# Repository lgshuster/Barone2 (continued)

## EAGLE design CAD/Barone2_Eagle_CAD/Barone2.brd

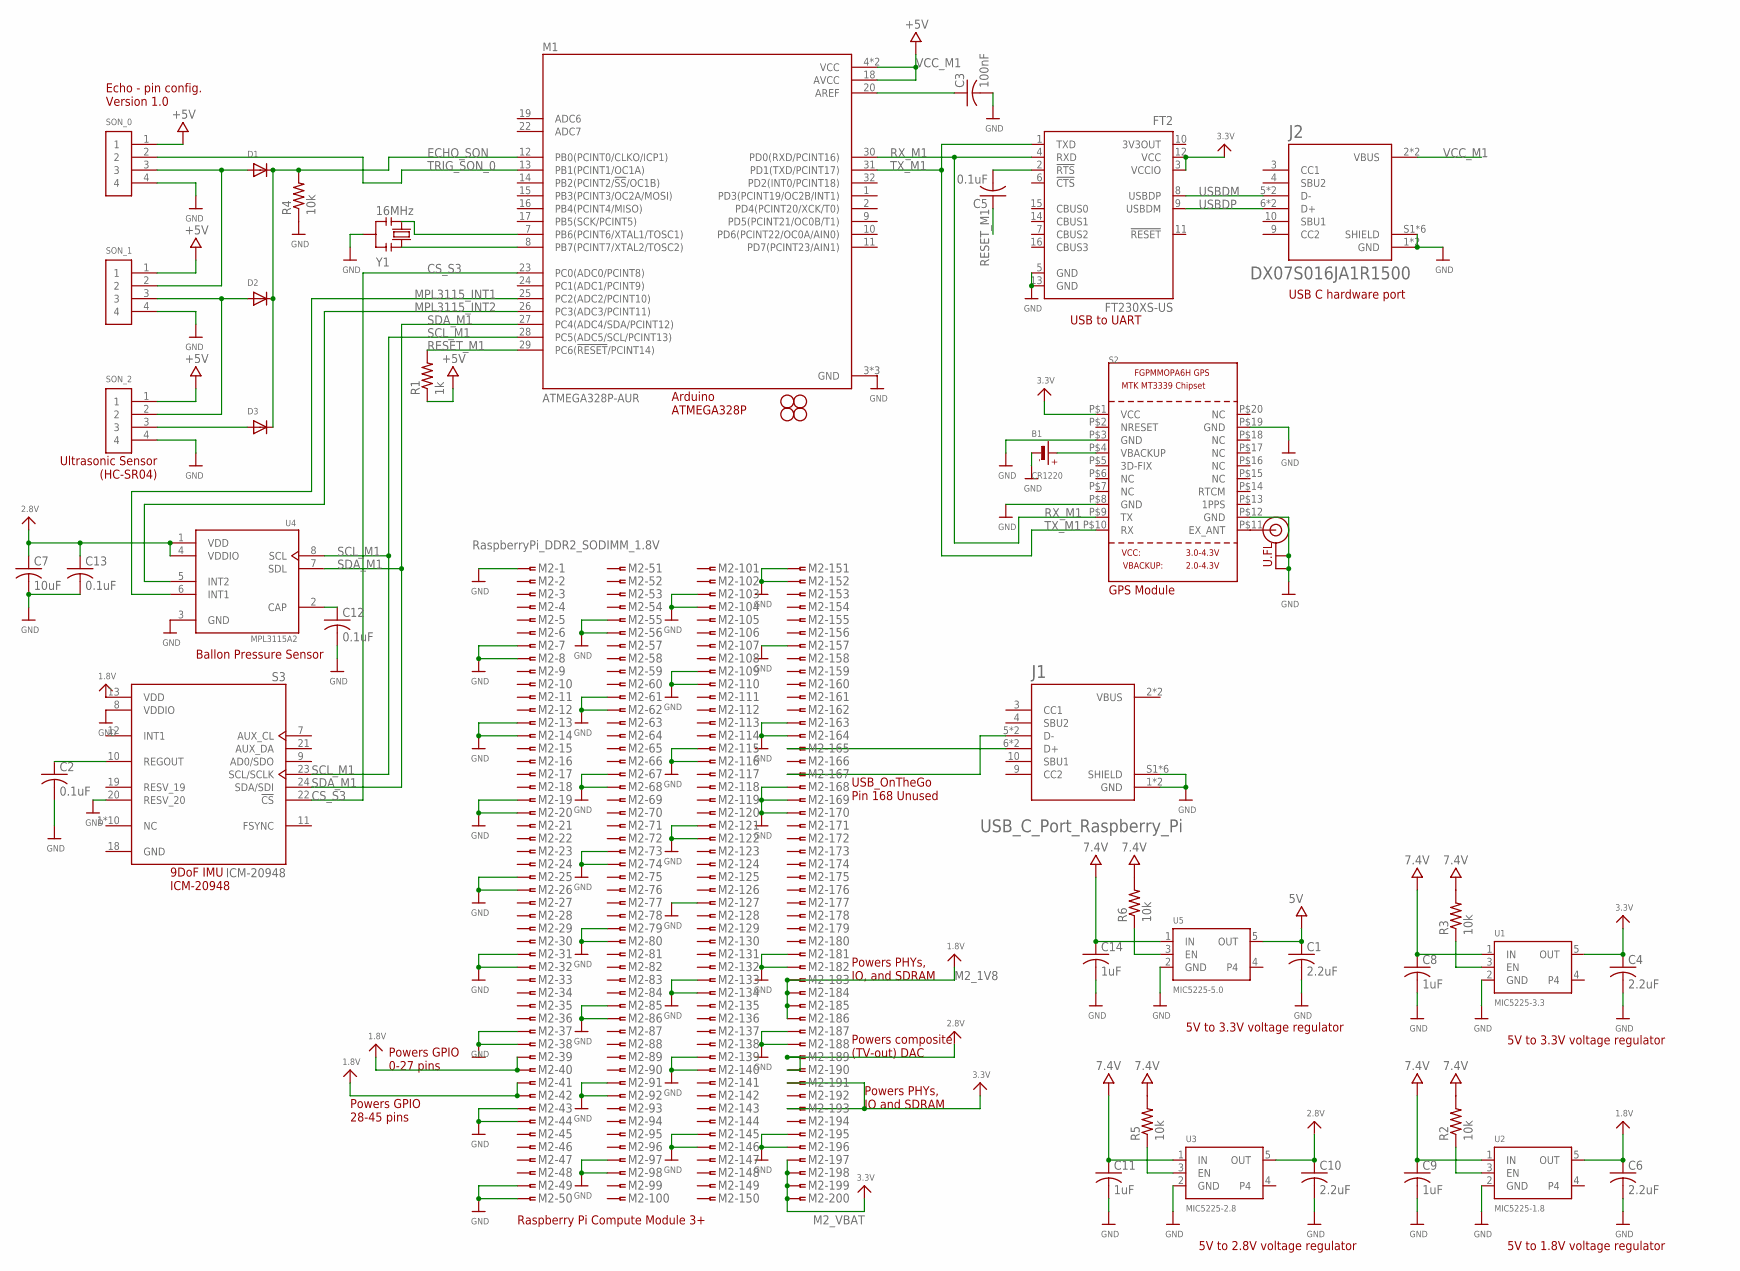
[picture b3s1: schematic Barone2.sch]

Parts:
B1: CR1220
C1, C4, C6, C10: 2.2uF; C0805
C2, C5, C12, C13: 0.1uF; C0805
C3: 100nF; C0805
C7: 10uF; C0805
C8, C9, C11, C14: 1uF; C0805
D1, D2, D3: DIODESOD-323F; SOD-323F
FT2: FT230XS-US; SSOP16
H1, H2, H3, H4: STAND-OFF
J1: USB_C_Port_Raspberry_Pi; JAE_DX07S016JA1R1500
J2: DX07S016JA1R1500; JAE_DX07S016JA1R1500
M1: ATMEGA328P-AUR; QFP80P900X900X120-32N
M2: RaspberryPi_DDR2_SODIMM_1.8V; SLOT-1376408-1_1.8V
R1: 1k; R0805W
R2, R3, R4, R5, R6: 10k; R0805W
S2: GPS_FGPMMOPA6H; FGPMMOPA6H
S3: ICM-20948; QFN40P300X300X105-24N
SON_0, SON_1, SON_2: 1X4-BIG; 1X04-BIG
U1: MIC5225-3.3; SOT23-5
U2: MIC5225-1.8; SOT23-5
U3: MIC5225-2.8; SOT23-5
U4: MPL3115A2; PSON125P300X500X120-8N
U5: MIC5225-5.0; SOT23-5
U.FL: U.FL
Y1: 16MHz; RESONATOR

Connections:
+5V: C14.1, R1.1, R2.2, R3.2, R5.2, R6.2, SON_0.1, SON_1.1, SON_2.1, U5.1 (IN)
CS_S3: M1.23 (PC0(ADC0/PCINT8)), S3.22 (!CS)
ECHO_SON: D1.C, D2.C, D3.C, M1.12 (PB0(PCINT0/CLKO/ICP1)), R4.2
GND: B1.-, C1.2, C2.2, C3.2, C4.2, C6.2, C7.2, C8.2, C9.2, C10.2, C11.2, C12.2, C13.2, C14.2, FT2.5 (GND), FT2.13 (GND), J1.1 (GND), J1.12 (GND), J1.S1 (SHIELD), J1.S2 (SHIELD), J1.S3 (SHIELD), J1.S4 (SHIELD), J1.S5 (SHIELD), J1.S6 (SHIELD), J2.1 (GND), J2.12 (GND), J2.S1 (SHIELD), J2.S2 (SHIELD), J2.S3 (SHIELD), J2.S4 (SHIELD), J2.S5 (SHIELD), J2.S6 (SHIELD), M1.3 (GND), M1.5 (GND), M1.21 (GND), M2.1, M2.7, M2.8, M2.13, M2.14, M2.19, M2.20, M2.25, M2.26, M2.31, M2.32, M2.37, M2.38, M2.43, M2.44, M2.49, M2.50, M2.55, M2.56, M2.61, M2.62, M2.67, M2.68, M2.73, M2.74, M2.79, M2.80, M2.85, M2.86, M2.91, M2.92, M2.97, M2.98, M2.103, M2.104, M2.109, M2.110, M2.115, M2.116, M2.121, M2.122, M2.127, M2.133, M2.134, M2.139, M2.140, M2.145, M2.146, M2.151, M2.152, M2.157, M2.163, M2.164, M2.168, M2.169, M2.170, M2.181, M2.182, M2.187, M2.188, M2.195, M2.196, R4.1, S2.P$3 (GND), S2.P$8 (GND), S2.P$19 (GND), S3.8 (VDDIO), S3.18 (GND), S3.20 (RESV_20), SON_0.4, SON_1.4, SON_2.4, U1.2 (GND), U2.2 (GND), U3.2 (GND), U4.3 (GND), U5.2 (GND), Y1.2
M2_1V8: M2.183, M2.184, M2.185, M2.186
M2_VBAT: M2.197, M2.198, M2.199, M2.200
MPL3115_INT1: M1.25 (PC2(ADC2/PCINT10)), U4.6 (INT1)
MPL3115_INT2: M1.26 (PC3(ADC3/PCINT11)), U4.5 (INT2)
unnamed: C3.1, M1.20 (AREF)
unnamed: S2.P$12 (GND), U.FL.P$1 (GND), U.FL.P$2 (GND)
unnamed: S2.P$11 (EX_ANT), U.FL.P$3 (SIGNAL)
unnamed: R3.1, U1.3 (EN)
unnamed: B1.+$1 (+), B1.+$2 (+), S2.P$4 (VBACKUP)
unnamed: R2.1, U2.3 (EN)
unnamed: J1.6 (D+), J1.7 (D+), M2.165
unnamed: J1.5 (D-), J1.8 (D-), M2.167
unnamed: M2.39, M2.40
unnamed: C12.1, U4.2 (CAP)
unnamed: R6.1, U5.3 (EN)
unnamed: R5.1, U3.3 (EN)
unnamed: D1.A, SON_0.3, SON_1.2
unnamed: D2.A, SON_1.3, SON_2.2
unnamed: M2.41, M2.42
unnamed: C8.1, U1.1 (IN)
unnamed: C5.2, FT2.2 (!RTS)
unnamed: D3.A, SON_2.3
unnamed: C9.1, U2.1 (IN)
unnamed: C11.1, U3.1 (IN)
unnamed: M1.7 (PB6(PCINT6/XTAL1/TOSC1)), Y1.3
unnamed: M1.8 (PB7(PCINT7/XTAL2/TOSC2)), Y1.1
unnamed: C2.1, S3.10 (REGOUT)
OUT: C1.1, C4.1, C6.1, C10.1, U1.5 (OUT), U2.5 (OUT), U3.5 (OUT), U5.5 (OUT)
RESET_M1: C5.1, M1.29 (PC6(!RESET!/PCINT14)), R1.2
RX_M1: FT2.4 (RXD), M1.30 (PD0(RXD/PCINT16)), S2.P$9 (TX)
SCL_M1: M1.28 (PC5(ADC5/SCL/PCINT13)), S3.23 (SCL/SCLK), U4.8 (SCL)
SDA_M1: M1.27 (PC4(ADC4/SDA/PCINT12)), S3.24 (SDA/SDI), U4.7 (SDL)
TRIG_SON_0: M1.13 (PB1(PCINT1/OC1A)), SON_0.2
TX_M1: FT2.1 (TXD), M1.31 (PD1(TXD/PCINT17)), S2.P$10 (RX)
USBDM: FT2.8 (USBDP), J2.5 (D-), J2.8 (D-)
USBDP: FT2.9 (USBDM), J2.6 (D+), J2.7 (D+)
VBUS: J1.2 (VBUS), J1.11 (VBUS)
VCC_M1: J2.2 (VBUS), J2.11 (VBUS), M1.4 (VCC), M1.6 (VCC), M1.18 (AVCC)
VIN: C7.1, C13.1, FT2.3 (VCCIO), FT2.12 (VCC), M2.189, M2.190, M2.191, M2.193, S2.P$1 (VCC), S3.13 (VDD), U4.1 (VDD), U4.4 (VDDIO)

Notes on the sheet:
9DoF IMU ICM-20948
Ultrasonic Sensor (HC-SR04)
USB to UART
Arduino ATMEGA328P
GPS Module
USB C hardware port
5V to 3.3V voltage regulator
Ballon Pressure Sensor
Raspberry Pi Compute Module 3+
5V to 1.8V voltage regulator
USB_OnTheGo Pin 168 Unused
Powers PHYs, IO and SDRAM
U.FL
Powers PHYs, IO, and SDRAM
5V to 2.8V voltage regulator
Powers composite (TV-out) DAC
Powers GPIO 0-27 pins
Powers GPIO 28-45 pins
Echo - pin config. Version 1.0

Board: 4 copper layers, 45 parts (0 on the bottom side), 43 nets, no tracks yet.

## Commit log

2021-03-06 Set up folders for ECE121 work
2021-03-06 Added folder for ECE121 Lab Manuals
2021-03-06 Create Lab2
2021-03-07 Create Family Reference Manual
2021-03-13 Deleted all previous files in Ryan's folder, added entire git repository from ECE121
2021-03-13 Wiring diagram and Board diagram V1.9
2021-03-15 wiring up board
2021-03-19 Added ballon pressure sensor, oscillators, logic level convers
2021-03-21 added logic level converter for interupt pin of IMU
2021-03-28 Added Transmitter pinout
2021-03-30 Fixing ECE121 source code
2021-03-30 60% complete with board wiring
2021-03-30 Jeremy's projects added
2021-03-31 Wiring diagram incomplete, 3.3V and GND via holes bug exists
2021-04-01 Fixed some minor bugs in V1.9 board wiring
2021-04-01 Fixed GND and 3.3V via issues, currently validating DRC errors
2021-04-02 Added GND to A0 pin of ICM-20948 IMU sensor, removed one 1.8V and 5.0V voltage regulators.
2021-04-03 v1.9 finalized and sent to board house OSH Park
2021-04-05 Matrix Multiplication Work Incomplete
2021-04-05 Matrix Multiply completed
2021-04-05 Matrix Scalar Multiply and Add done
2021-04-07 Determinant Done, working on Inverse
2021-04-07 Inverse finished
2021-04-08 Final Adjustments to Matrix code
2021-04-10 Cross Product finished and other functions optimized
2021-04-15 Height.c added
2021-04-20 Tracking height forward and below sensors
2021-04-20 Height tracking code
2021-04-20 Final Height Push
2021-06-07 Create test
2021-06-07 Dylans Solidworks and Matlab Files
2021-06-07 moving some files to correct folders
2021-06-07 Isaacs V-REP SIM Files
2021-06-08 Geroges Contol files
